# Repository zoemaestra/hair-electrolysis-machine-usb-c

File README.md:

# Hair Electrolysis Machine v4.1

### DIY electrolysis carries risk of permanent scarring if done improperly. If something goes wrong, only you are responsible.

---

If you would like a single, pre-assembled unit with the foot pedal, stylus and pads included I now sell these on my store: https://shop.imzoe.me/products/portable-galvanic-electrolysis-hair-removal-device

This is based on n3tcat's original design but redesigned around the STM32 to cut down the BOM and make the board single sided. Unlike v3.4, the board requires no soldering to assemble (soldering is still required to build the stylus and foot pedal), just a 340mAh LiPo battery and a display which can just be plugged in. It is even cheaper and even easier to assemble at approximately £15/$20 per board!

You should really read the guide on how to order, assemble and use: https://imzoe.me/projects/electrolysis/electrolysis

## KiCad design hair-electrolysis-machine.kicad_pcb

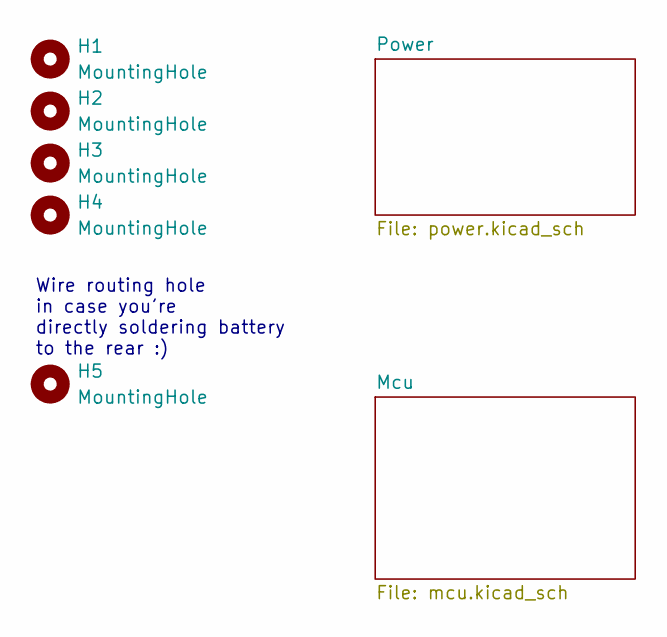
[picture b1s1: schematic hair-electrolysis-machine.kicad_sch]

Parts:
H1, H2, H3, H4: MountingHole; MountingHole_3.2mm_M3
H5: MountingHole; MountingHole_2.5mm

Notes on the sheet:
Wire routing hole in case you're directly soldering battery to the rear :)

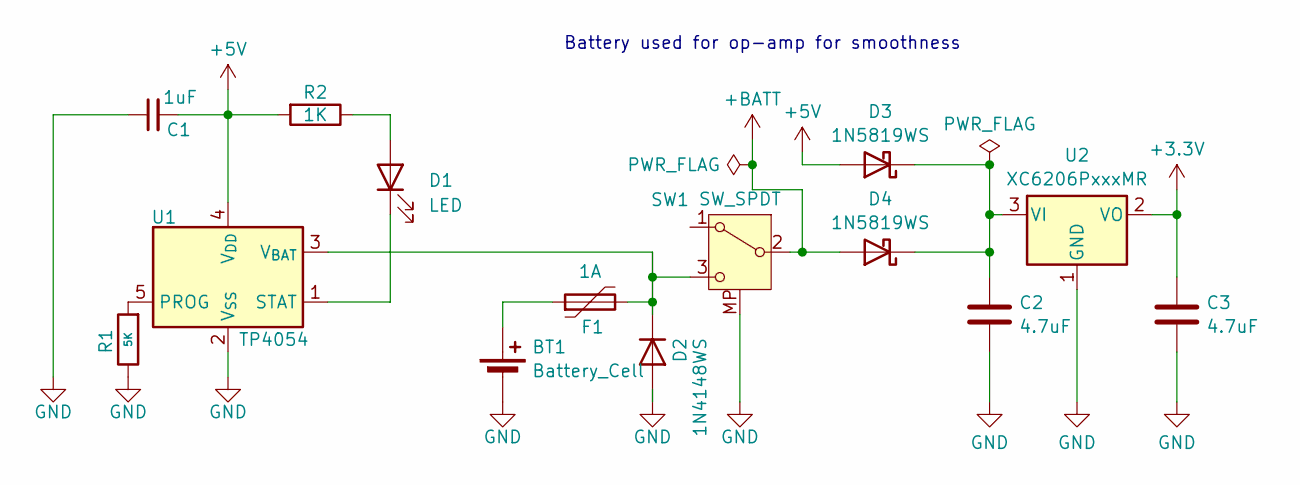
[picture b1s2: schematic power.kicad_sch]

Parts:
BT1: Battery_Cell; JST_PH_S2B-PH-K_1x02_P2.00mm_Horizontal; LCSC C16965
C1: 1uF; C_0603_1608Metric; LCSC C15849
C2, C3: 4.7uF; C_0805_2012Metric; LCSC C1779
D1: LED; LED_0805_2012Metric; LCSC C84256
D2: 1N4148WS; D_SOD-323; LCSC C2128
D3, D4: 1N5819WS; D_SOD-323; LCSC C191023
F1: 1A; Fuse_0805_2012Metric; LCSC C269104
R1: 5K; R_0603_1608Metric; LCSC C862232
R2: 1K; R_0603_1608Metric; LCSC C21190
SW1: SW_SPDT; SW_Slide_SPDT_Angled_CK_OS102011MA1Q; LCSC C131374
U1: TP4054; SOT-23-5; LCSC C668215
U2: XC6206PxxxMR; SOT-23-3; LCSC C5446

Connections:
+3.3V: C3.1, U2.2 (VO); also elsewhere on the board
+5V: C1.2, D3.2 (A), R2.2, U1.4 (V_{DD}); also elsewhere on the board
+BATT: D4.2 (A), SW1.2 (B); also elsewhere on the board
GND: BT1.2 (-), C1.1, C2.2, C3.2, D2.2 (A), R1.1, SW1.MP, U1.2 (V_{SS}), U2.1 (GND); also elsewhere on the board
unnamed: BT1.1 (+), F1.1
unnamed: D1.2 (A), R2.1
unnamed: D1.1 (K), U1.1 (STAT)
unnamed: D2.1 (K), F1.2, SW1.3 (C), U1.3 (V_{BAT})
unnamed: C2.1, D3.1 (K), D4.1 (K), U2.3 (VI)
unnamed: R1.2, U1.5 (PROG)

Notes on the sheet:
Battery used for op-amp for smoothness

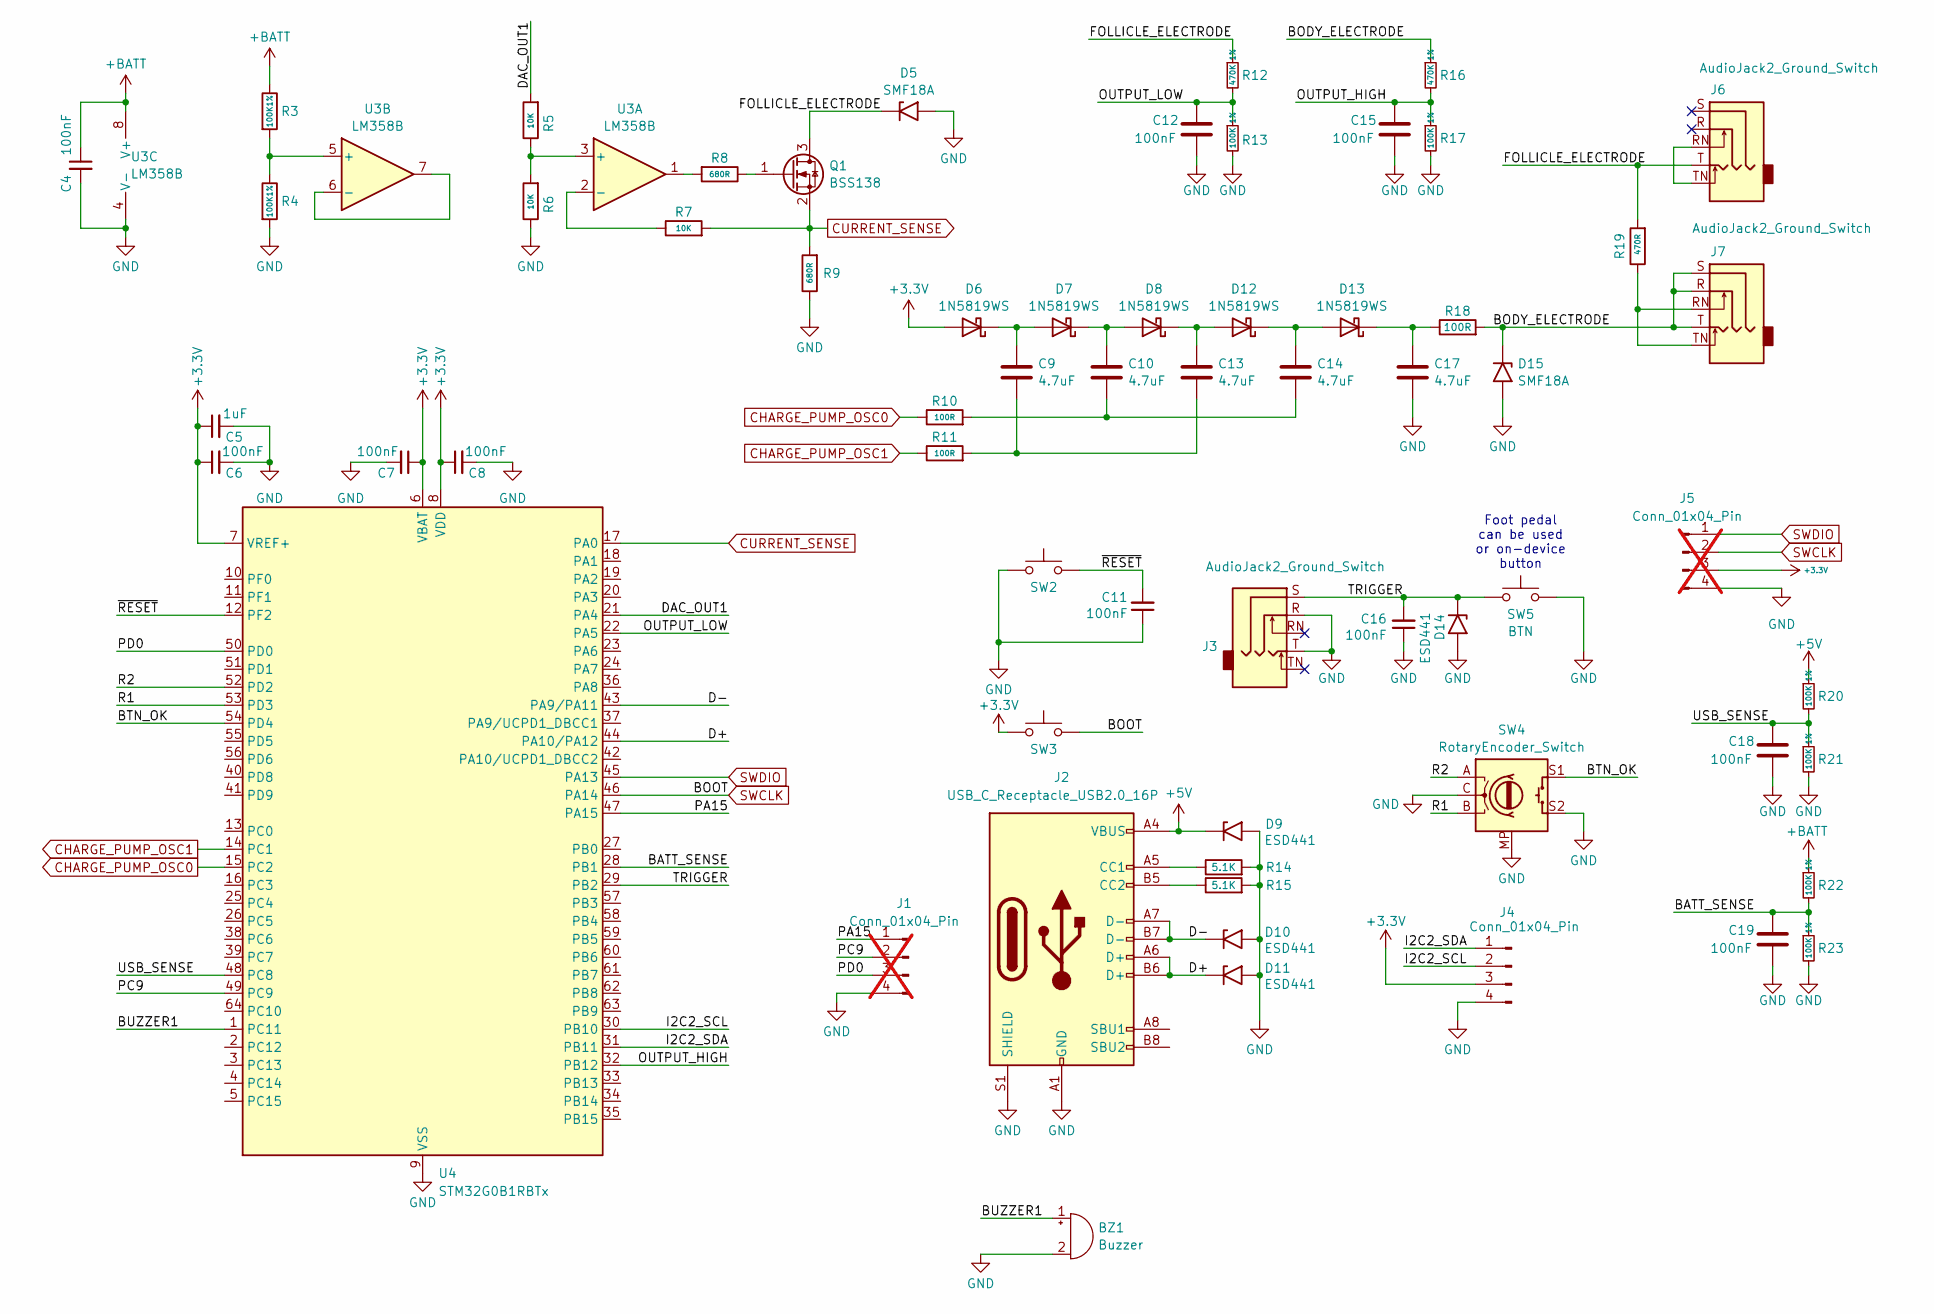
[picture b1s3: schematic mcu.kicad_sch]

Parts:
BZ1: Buzzer; Buzzer_TDK_PS1240P02BT_D12.2mm_H6.5mm; LCSC C76871
C4, C6, C7, C8, C11, C12, C15, C16, C18, C19: 100nF; C_0603_1608Metric; LCSC C14663
C5: 1uF; C_0603_1608Metric; LCSC C15849
C9, C10, C13, C14, C17: 4.7uF; C_0805_2012Metric; LCSC C1779
D5, D15: SMF18A; D_SMF; LCSC C169433
D6, D7, D8, D12, D13: 1N5819WS; D_SOD-323; LCSC C191023
D9, D10, D11, D14: ESD441; D_0402_1005Metric; LCSC C316049
J1: Conn_01x04_Pin; PinHeader_1x04_P2.54mm_Vertical; not fitted
J2: USB_C_Receptacle_USB2.0_16P; USB_C_Receptacle_HRO_TYPE-C-31-M-12; LCSC C165948
J3, J6: AudioJack2_Ground_Switch; Jack_3.5mm_CUI_SJ1-3525N_Horizontal; LCSC C16684
J4: Conn_01x04_Pin; PinSocket_1x04_P2.54mm_Vertical; LCSC C2718488
J5: Conn_01x04_Pin; PinSocket_1x04_P2.54mm_Vertical; not fitted
J7: AudioJack2_Ground_Switch; Jack_2.5mm_PJ242_6P_12x6.2x4mm_Horizontal; LCSC C431536
Q1: BSS138; SOT-23; LCSC C8490
R3, R4: 100K1%; R_0603_1608Metric_Pad0.98x0.95mm_HandSolder; LCSC C25803
R5, R6, R7: 10K; R_0603_1608Metric_Pad0.98x0.95mm_HandSolder; LCSC C25804
R8, R9: 680R; R_0603_1608Metric_Pad0.98x0.95mm_HandSolder; LCSC C23228
R10, R11, R18: 100R; R_0603_1608Metric; LCSC C22775
R12, R16: 470K 1%; R_0603_1608Metric; LCSC C23178
R13, R17, R20, R21, R22, R23: 100K 1%; R_0603_1608Metric; LCSC C25803
R14, R15: 5.1K; R_0603_1608Metric; LCSC C23186
R19: 470R; R_0603_1608Metric_Pad0.98x0.95mm_HandSolder; LCSC C23179
SW2, SW3, SW5: BTN; SW_SPST_TS-1088-xR025; LCSC C720477
SW4: RotaryEncoder_Switch; RotaryEncoder_Alps_EC11E-Switch_Vertical_H20mm; LCSC C2991196
U3: LM358B; SOIC-8_3.9x4.9mm_P1.27mm; LCSC C1850238
U4: STM32G0B1RBTx; LQFP-64_10x10mm_P0.5mm; LCSC C5143679

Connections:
+3.3V: C5.1, C6.1, C7.1, C8.1, D6.2 (A), J4.3, J5.3, SW3.2, U4.6 (VBAT), U4.7 (VREF+), U4.8 (VDD); also elsewhere on the board
+5V: D9.1 (A1), J2.A4 (VBUS), J2.A9 (VBUS), J2.B4 (VBUS), J2.B9 (VBUS), R20.1; also elsewhere on the board
+BATT: C4.1, R3.1, R22.1, U3.8 (V+); also elsewhere on the board
/Mcu/BATT_SENSE: C19.1, R22.2, R23.1, U4.28 (PB1)
/Mcu/BODY_ELECTRODE: D15.1 (A1), J7.R, J7.S, J7.T, R16.1, R18.2
/Mcu/BTN_OK: SW4.S1, U4.54 (PD4)
/Mcu/BUZZER1: BZ1.1 (+), U4.1 (PC11)
/Mcu/D+: D11.1 (A1), J2.A6 (D+), J2.B6 (D+), U4.44 (PA10/PA12)
/Mcu/D-: D10.1 (A1), J2.A7 (D-), J2.B7 (D-), U4.43 (PA9/PA11)
/Mcu/DAC_OUT1: R5.2, U4.21 (PA4)
/Mcu/FOLLICLE_ELECTRODE: D5.1 (A1), J6.T, Q1.3 (D), R12.1, R19.2
/Mcu/I2C2_SCL: J4.2, U4.30 (PB10)
/Mcu/I2C2_SDA: J4.1, U4.31 (PB11)
/Mcu/OUTPUT_HIGH: C15.1, R16.2, R17.1, U4.32 (PB12)
/Mcu/OUTPUT_LOW: C12.1, R12.2, R13.1, U4.22 (PA5)
/Mcu/PA15: J1.1, U4.47 (PA15)
/Mcu/PC9: J1.2, U4.49 (PC9)
/Mcu/PD0: J1.3, U4.50 (PD0)
/Mcu/R1: SW4.B, U4.53 (PD3)
/Mcu/R2: SW4.A, U4.52 (PD2)
/Mcu/TRIGGER: C16.2, D14.1 (A1), J3.S, SW5.2, U4.29 (PB2)
/Mcu/USB_SENSE: C18.1, R20.2, R21.1, U4.48 (PC8)
/Mcu/~RESET: C11.2, SW2.1, U4.12 (PF2)
CHARGE_PUMP_OSC0: R10.1, U4.15 (PC2)
CHARGE_PUMP_OSC1: R11.1, U4.14 (PC1)
CURRENT_SENSE: Q1.2 (S), R7.2, R9.2, U4.17 (PA0)
GND: BZ1.2 (-), C4.2, C5.2, C6.2, C7.2, C8.2, C11.1, C12.2, C15.2, C16.1, C17.2, C18.2, C19.2, D5.2 (A2), D9.2 (A2), D10.2 (A2), D11.2 (A2), D14.2 (A2), D15.2 (A2), J1.4, J2.A1 (GND), J2.A12 (GND), J2.B1 (GND), J2.B12 (GND), J2.S1 (SHIELD), J3.R, J3.T, J4.4, J5.4, R4.2, R6.1, R9.1, R13.2, R14.2, R15.2, R17.2, R21.2, R23.2, SW2.2, SW4.C, SW4.MP, SW4.S2, SW5.1, U3.4 (V-), U4.9 (VSS); also elsewhere on the board
unnamed: C10.2, C14.2, R10.2
unnamed: C9.2, C13.2, R11.2
unnamed: C9.1, D6.1 (K), D7.2 (A)
unnamed: C10.1, D7.1 (K), D8.2 (A)
unnamed: C13.1, D8.1 (K), D12.2 (A)
unnamed: C14.1, D12.1 (K), D13.2 (A)
unnamed: C17.1, D13.1 (K), R18.1
unnamed: J2.A5 (CC1), R14.1
unnamed: J2.B5 (CC2), R15.1
unnamed: J6.RN, J6.TN
unnamed: J7.RN, J7.TN, R19.1
unnamed: Q1.1 (G), R8.1
unnamed: R8.2, U3.1
unnamed: R5.1, R6.2, U3.3 (+)
unnamed: R7.1, U3.2 (-)
unnamed: R3.2, R4.1, U3.5 (+)
unnamed: U3.6 (-), U3.7
SWCLK: J5.2, SW3.1, U4.46 (PA14)
SWDIO: J5.1, U4.45 (PA13)

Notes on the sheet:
Foot pedal can be used or on-device button

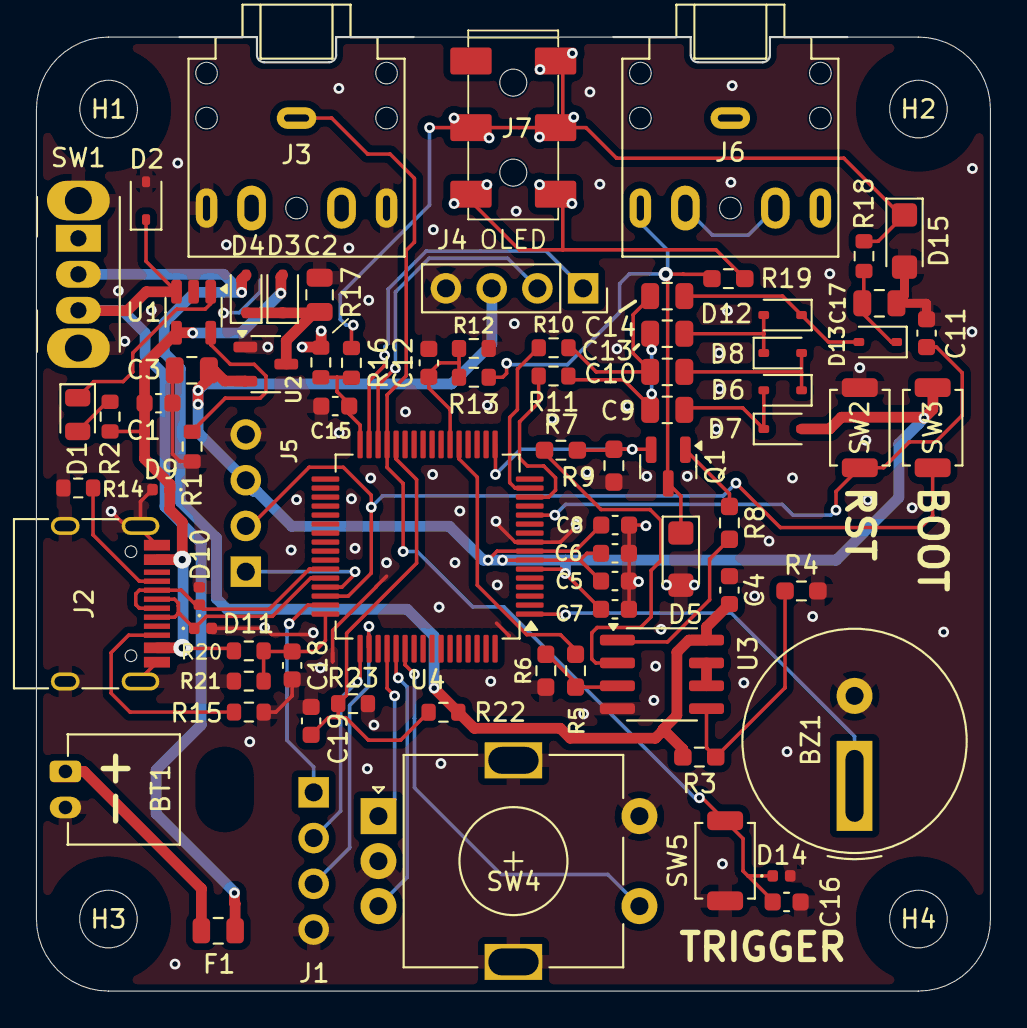
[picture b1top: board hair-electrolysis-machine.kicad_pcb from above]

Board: 2 copper layers, 52.9 x 53.0 mm, 82 parts (0 on the bottom side), 52 nets.

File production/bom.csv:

Designator,Footprint,Quantity,Value,LCSC Part #
BT1,JST_PH_S2B-PH-K_1x02_P2.00mm_Horizontal,1,Battery_Cell,C16965
BZ1,Buzzer_TDK_PS1240P02BT_D12.2mm_H6.5mm,1,Buzzer,C76871
"C1, C5",0603,2,1uF,C15849
"C10, C13, C14, C17, C2, C3, C9",0805,7,4.7uF,C1779
"C11, C12, C15, C16, C18, C19, C4, C6, C7, C8",0603,10,100nF,C14663
D1,0805,1,LED,C84256
"D10, D11, D14, D9",0402,4,ESD441,C316049
"D12, D13, D3, D4, D6, D7, D8",D_SOD-323,7,1N5819WS,C191023
"D15, D5",D_SMF,2,SMF18A,C169433
D2,D_SOD-323,1,1N4148WS,C2128
F1,0805,1,1A,C269104
J2,USB_C_Receptacle_HRO_TYPE-C-31-M-12,1,USB_C_Receptacle_USB2.0_16P,C165948
"J3, J6",Jack_3.5mm_CUI_SJ1-3525N_Horizontal,2,AudioJack2_Ground_Switch,C16684
J4,PinSocket_1x04_P2.54mm_Vertical,1,Conn_01x04_Pin,C2718488
J7,Jack_2.5mm_PJ242_6P_12x6.2x4mm_Horizontal,1,AudioJack2_Ground_Switch,C431536
Q1,SOT-23,1,BSS138,C8490
R1,0603,1,2.7K,C13167
"R10, R11, R18",0603,3,100R,C22775
"R12, R16",0603,2,470K 1%,C23178
"R13, R17, R20, R21, R22, R23",0603,6,100K 1%,C25803
"R14, R15",0603,2,5.1K,C23186
R19,0603,1,470R,C23179
R2,0603,1,1K,C21190
"R3, R4",0603,2,100K1%,C25803
"R5, R6, R7",0603,3,10K,C25804
"R8, R9",0603,2,680R,C23228
SW1,SW_Slide_SPDT_Angled_CK_OS102011MA1Q,1,SW_SPDT,C131374
"SW2, SW3, SW5",SW_SPST_TS-1088-xR025,3,BTN,C720477
SW4,RotaryEncoder_Alps_EC11E-Switch_Vertical_H20mm,1,RotaryEncoder_Switch,C2991196
U1,SOT-23-5,1,TP4054,C668215
U2,SOT-23-3,1,XC6206PxxxMR,C5446
U3,SOIC-8_3.9x4.9mm_P1.27mm,1,LM358B,C1850238
U4,LQFP-64_10x10mm_P0.5mm,1,STM32G0B1RBTx,C5143679

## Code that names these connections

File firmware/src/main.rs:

#![no_std]
#![no_main]

mod app;
mod button;
mod buzzer;
mod charge_pump;
mod current_dac;
#[path = "../../src/gui/mod.rs"]
mod gui;
mod meter;
mod output_handler;
mod safety;
mod settings;

use core::sync::atomic::Ordering;

use app::App;
use buzzer::{BUZZER_COMMAND_CHANNEL, Buzzer};
use charge_pump::ChargePump;
use current_dac::CurrentDac;
use embassy_executor::Spawner;
use embassy_futures::select::{Either, select};
use embassy_stm32::{
    bind_interrupts, dma,
    exti::{self, ExtiInput},
    flash::Flash,
    gpio::{Input, Pull},
    i2c::{self, I2c},
    peripherals::{DMA1_CH1, DMA1_CH2, I2C2},
};
use embassy_time::Timer;
use meter::Meter;
use output_handler::OutputHandler;
use portable_atomic::AtomicI32;
use safety::USB_CONNECTED;
use settings::SettingsStore;

use defmt_rtt as _;

bind_interrupts!(struct Irqs {
    I2C2_3 => i2c::EventInterruptHandler<I2C2>, i2c::ErrorInterruptHandler<I2C2>;
    DMA1_CHANNEL1 => dma::InterruptHandler<DMA1_CH1>;
    DMA1_CHANNEL2_3 => dma::InterruptHandler<DMA1_CH2>;
    EXTI2_3 => exti::InterruptHandler<embassy_stm32::interrupt::typelevel::EXTI2_3>;
});

static ENCODER_DELTA: AtomicI32 = AtomicI32::new(0);

#[embassy_executor::task]
async fn encoder(
    mut r1: ExtiInput<'static, embassy_stm32::mode::Async>,
    mut r2: ExtiInput<'static, embassy_stm32::mode::Async>,
) {
    let mut previous = ((r1.is_high() as u8) << 1) | r2.is_high() as u8;
    let mut steps = 0i8;

    loop {
        match select(r1.wait_for_any_edge(), r2.wait_for_any_edge()).await {
            Either::First(_) | Either::Second(_) => {}
        }

        // Contact debounce settling (1 ms)
        Timer::after_millis(1).await;
        let current = ((r1.is_high() as u8) << 1) | r2.is_high() as u8;
        const STEP: [i8; 16] = [0, -1, 1, 0, 1, 0, 0, -1, -1, 0, 0, 1, 0, 1, -1, 0];
        steps += STEP[((previous << 2) | current) as usize];
        previous = current;

        if steps <= -2 {
            ENCODER_DELTA.fetch_add(1, Ordering::Relaxed);
            steps = 0;
        } else if steps >= 2 {
            ENCODER_DELTA.fetch_add(-1, Ordering::Relaxed);
            steps = 0;
        }
    }
}

#[embassy_executor::task]
async fn buzzer_handler(mut buzzer: Buzzer<'static>) {
    loop {
        buzzer.play(BUZZER_COMMAND_CHANNEL.receive().await).await;
    }
}

#[embassy_executor::task]
async fn store_handler(mut store: SettingsStore<'static>) {
    store.tick_forever().await;
}

#[embassy_executor::task]
async fn output_task(mut handler: OutputHandler<'static>) {
    handler.tick_forever().await;
}

#[embassy_executor::task]
async fn usb_monitor(input: Input<'static>) {
    let mut stable = input.is_high();
    USB_CONNECTED.store(stable, Ordering::Relaxed);
    let mut count: u8 = 0;
    loop {
        let sample = input.is_high();
        if sample != stable {
            count += 1;
            if count >= 25 {
                // 50 ms of consistent new state required to switch
                stable = sample;
                USB_CONNECTED.store(stable, Ordering::Relaxed);
                count = 0;
            }
        } else {
            count = 0;
        }
        Timer::after_millis(2).await;
    }
}

#[embassy_executor::main]
async fn main(spawner: Spawner) {
    let mut config = embassy_stm32::Config::default();
    config.rcc.pll = Some(embassy_stm32::rcc::Pll {
        source: embassy_stm32::rcc::PllSource::HSI,
        prediv: embassy_stm32::rcc::PllPreDiv::DIV1,
        mul: embassy_stm32::rcc::PllMul::MUL8,
        divp: None,
        divq: None,
        divr: Some(embassy_stm32::rcc::PllRDiv::DIV2),
    });
    config.rcc.sys = embassy_stm32::rcc::Sysclk::PLL1_R;
    let p = embassy_stm32::init(config);

    let store = SettingsStore::new(Flash::new_blocking(p.FLASH)).await;
    spawner.spawn(store_handler(store)).unwrap();

    let r2 = ExtiInput::new(p.PD2, p.EXTI2, Pull::Up, Irqs);
    let r1 = ExtiInput::new(p.PD3, p.EXTI3, Pull::Up, Irqs);
    spawner.spawn(encoder(r1, r2)).unwrap();

    spawner
        .spawn(buzzer_handler(Buzzer::new(p.TIM1, p.PC11)))
        .unwrap();

    spawner
        .spawn(usb_monitor(Input::new(p.PC8, Pull::None)))
        .unwrap();

    let meter = Meter::new(p.ADC1, p.PA0, p.PB1, p.PA5, p.PB12);
    let dac = CurrentDac::new(p.DAC1, p.PA4);
    let pump = ChargePump::new(p.TIM15, p.PC1, p.PC2);
    spawner
        .spawn(output_task(OutputHandler::new(
            pump, dac, meter, p.PB2, p.IWDG,
        )))
        .unwrap();

    let mut i2c_config = i2c::Config::default();
    i2c_config.frequency = embassy_stm32::time::Hertz(400_000);
    let display_i2c = I2c::new(
        p.I2C2, p.PB10, p.PB11, p.DMA1_CH1, p.DMA1_CH2, Irqs, i2c_config,
    );
    let mut app = App::new(display_i2c, p.PD4).await;

    loop {
        app.scroll(ENCODER_DELTA.swap(0, Ordering::Relaxed)).await;
        app.render().await;
        Timer::after_millis(5).await;
    }
}

#[panic_handler]
fn panic(_info: &core::panic::PanicInfo) -> ! {
    // Reset immediately: peripheral reset states disable TIM15 and DAC1.
    cortex_m::peripheral::SCB::sys_reset()
}

#[cortex_m_rt::exception]
unsafe fn HardFault(_frame: &cortex_m_rt::ExceptionFrame) -> ! {
    cortex_m::peripheral::SCB::sys_reset()
}

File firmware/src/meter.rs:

use embassy_stm32::{
    Peri,
    adc::{Adc, SampleTime, VREF_CALIB_MV, VrefInt},
    peripherals::{ADC1, PA0, PA5, PB1, PB12},
};

pub struct Meter<'a> {
    adc: Adc<'a, ADC1>,
    current: Peri<'a, PA0>,
    battery: Peri<'a, PB1>,
    output_low: Peri<'a, PA5>,
    output_high: Peri<'a, PB12>,
    vref: VrefInt,
}

impl<'a> Meter<'a> {
    pub fn new(
        adc: Peri<'a, ADC1>,
        current: Peri<'a, PA0>,
        battery: Peri<'a, PB1>,
        output_low: Peri<'a, PA5>,
        output_high: Peri<'a, PB12>,
    ) -> Self {
        let adc = Adc::new(adc);
        let vref = adc.enable_vrefint();
        Self {
            adc,
            current,
            battery,
            output_low,
            output_high,
            vref,
        }
    }

    fn vdda(&mut self) -> f64 {
        let raw = self
            .adc
            .blocking_read(&mut self.vref, SampleTime::CYCLES160_5);
        if raw == 0 {
            return 3.3;
        }
        VREF_CALIB_MV as f64 * self.vref.calibrated_value() as f64 / raw as f64 / 1000.0
    }

    fn read_voltage<P: embassy_stm32::adc::AdcChannel<ADC1>>(
        adc: &mut Adc<'a, ADC1>,
        pin: &mut P,
        vdda: f64,
    ) -> f64 {
        // average eight conversions here to reduce regulator and pump noise.
        let mut sum = 0u32;
        for _ in 0..8 {
            sum += adc.blocking_read(pin, SampleTime::CYCLES160_5) as u32;
        }
        (sum as f64 / 8.0) * vdda / 4095.0
    }

    pub fn battery_voltage(&mut self) -> f64 {
        let vdda = self.vdda();
        Self::read_voltage(&mut self.adc, &mut self.battery, vdda) * 2.0
    }

    pub fn charge_pump_voltage(&mut self) -> f64 {
        let vdda = self.vdda();
        Self::read_voltage(&mut self.adc, &mut self.output_high, vdda) * 5.7
    }

    pub fn low_side_voltage(&mut self) -> f64 {
        let vdda = self.vdda();
        Self::read_voltage(&mut self.adc, &mut self.output_low, vdda) * 5.7
    }

    pub fn delta_voltage(&mut self) -> f64 {
        self.charge_pump_voltage() - self.low_side_voltage()
    }

    pub fn measure_current_ma(&mut self) -> f64 {
        let vdda = self.vdda();
        Self::read_voltage(&mut self.adc, &mut self.current, vdda) / 0.680
    }
}

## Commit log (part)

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2026-05-05 Project details and BOM links
2026-05-05 formatting
2026-05-05 Add safety warning to README
2026-05-10 Added .stl files
2026-05-19 Improved case design & rotary encoder knob
2026-05-21 Minor modifications
    Knob allows for more travel for better clicks and switch hole is made larger so installation is easier
2026-05-21 Minor mounting alterations
    Mount holes are wide enough to take M3 screws through them
2026-05-21 Add screws to the components list in README
    Added a note about screws to the components list.
2026-05-21 Add image
    Removed outdated comment about mini USB cables.
2026-05-29 Revise README with cost breakdown and assembly notes
    Updated cost breakdown and additional details about assembly and components.
2026-06-18 Minor changes
    Moved 5v line out from under USB-C connector and changed buzzer pads so more common buzzers can more easily be used
2026-06-22 Added JLC BOM
2026-06-22 oops
2026-06-22 Update README with BOM details and additional items
    Added information about BOM usage and additional components.
2026-06-22 Minor D9 ground changes
2026-06-22 Uploading the right version this time...
